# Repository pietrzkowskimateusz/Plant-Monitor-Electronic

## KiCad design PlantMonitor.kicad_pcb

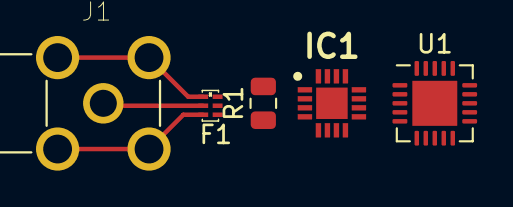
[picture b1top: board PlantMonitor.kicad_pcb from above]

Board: 2 copper layers, 5 parts (0 on the bottom side), 2 nets.

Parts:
F1: 2450LP14B100; 2450BM14A0002
IC1: RFX2401C; QFN50P300X300X60-17N-D
J1: 5-1814400-1; SMA_CONN_5-1814400-1
R1: R; R_0805_2012Metric
U1: nRF24L01P; QFN-20-1EP_4x4mm_P0.5mm_EP2.5x2.5mm

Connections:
GND: F1.1, F1.3, F1.4, F1.6, J1.1, J1.2, J1.3, J1.4
unnamed: F1.5, J1.5

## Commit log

2020-06-01 Creating KiCad Project
    Creating first schematics
2020-06-01 First revision of RF circuit
2020-06-01 Little Corrections
    Little corrections in RF circuit
